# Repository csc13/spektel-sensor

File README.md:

spektel-sensor
==============
*[See the project blog here!](http://spektel.cescholz.de/)* 

This is a small project for a XMEGA based sensor for the Spektrum-RC telemetry system.

The sensor is based on the flowing components:
- Atmel XMEGA32E5
- Allegro ACS758LCB-100U hall effect current sensor
- Bosch BMP180 pressure sensor (planned)

The firmware was developed in C using Atmel Studio 6 and the Atmel ASF framework.

	Note: The Spektrum RC TM1000 telemetry modul, a DSMX receiver with data port and a 
	transmitter with telemetry functions are required to use the sensor. Not all Spektrum RC telemetry able
	transmitters support all sensors. I use a DX9 for testing.

### Basic functions
The sensor measures 25 times a second the actual current, voltage and pressure. From this 
it calculates the used capacity, hight and climb rate.

- Show used capacity of main battery
- Show actual current of main battery
- Show actual voltage of main battery
- Show altitude
- Programmable via on button (change the battery capacity)

### Planned functions
- Show climb rate
- Show cell voltages of main battery

### Project Structure
- firmware (compiled firmware for XMEGA)
- flight_logs (from Spektrum transmitter)
- hardware (Eagle PCB files)
- pictures (photos)
- project (Atmel Studio, make files, etc.)
- src (C sources)

### History
#### 2014-10-28: Initial upload with REV_A board layout
- Please note that REV_A is the initial prototype and has several bugs

#### 2014-11-02: Added support for RealtimePlotter and arduplot
Two two great serial monitors based on Processing (https://www.processing.org/).
Please see https://github.com/sebnil/RealtimePlotter.git and see https://github.com/dahart/arduplot.git).

#### 2015-01-19: Added support for the REV_B board
This includes the smaller board, BMP180 altitude measurement, setup button, self calibration.

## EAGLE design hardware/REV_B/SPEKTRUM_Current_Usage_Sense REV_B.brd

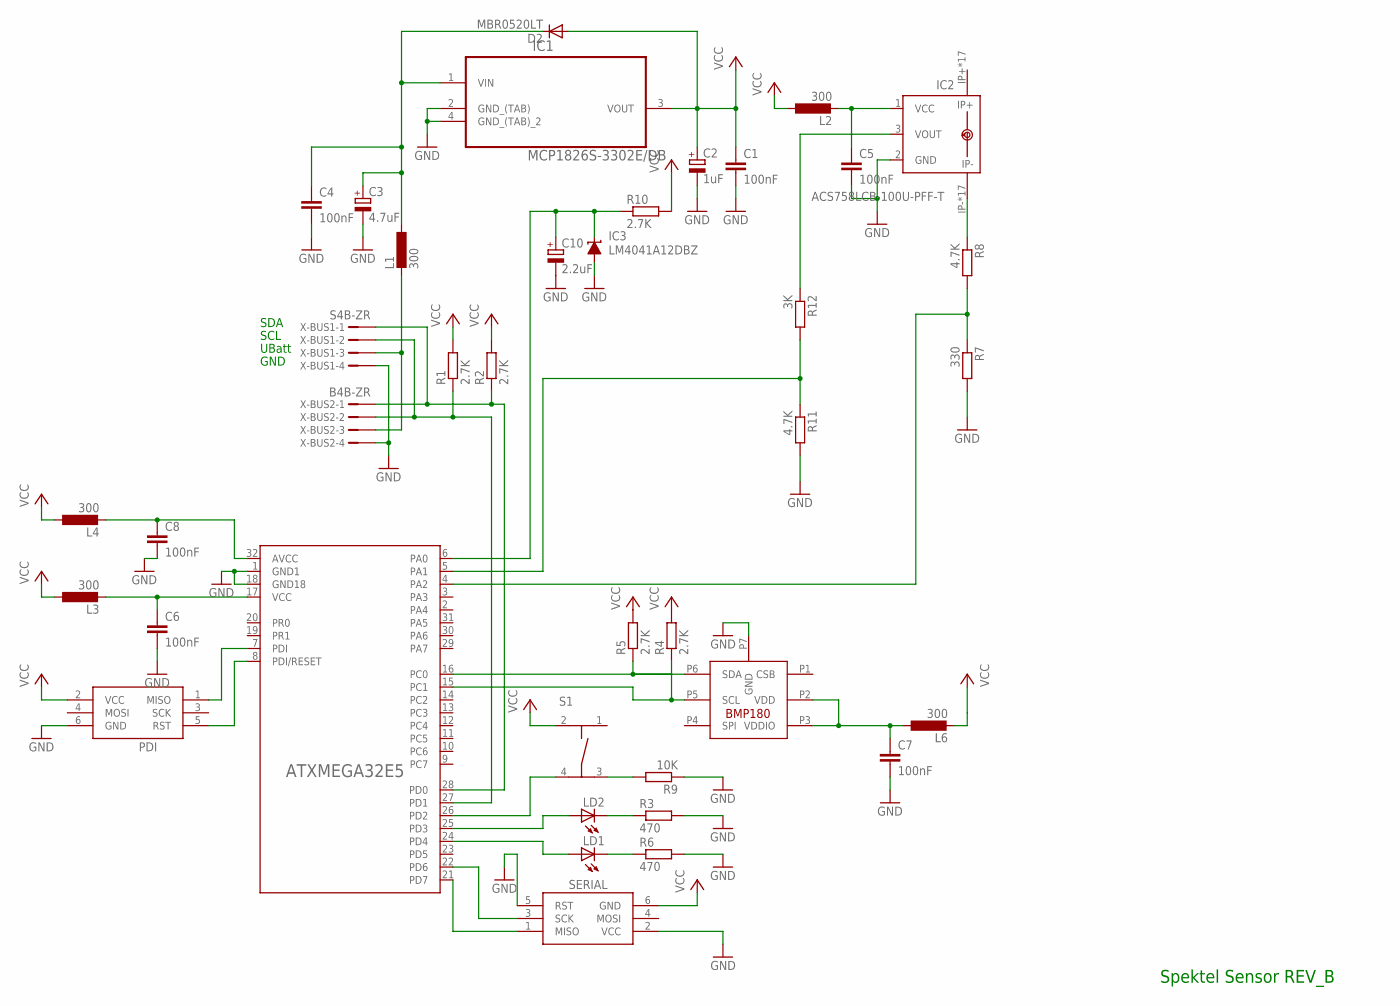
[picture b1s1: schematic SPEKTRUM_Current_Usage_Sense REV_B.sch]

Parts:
ATXMEGA32E5: ATXMEGA32E5/16E5/8E5ATXMEGA32E5-AU; TQFP32-08
BMP180: BMP180; BMP180_LGA7
C1, C4, C5, C6, C7, C8: 100nF; C0603
C2: 1uF; A/3216-18W
C3: 4.7uF; A/3216-18W
C10: 2.2uF; A/3216-18W
D2: MBR0520LT; SOD123
IC1: MCP1826S-3302E/DB; SOT230P700X180-4N
IC2: ACS758LCB-100U-PFF-T; CB-PFF; MPN ACS758LCB-100U-PFF-T
IC3: LM4041A12DBZ; DBZ_R-PDSO-G3
L1, L2, L3, L4, L6: 300; L0603
LD1, LD2: LEDCHIPLED_0603; CHIPLED_0603
PDI: AVRISP-6; AVRISP
R1, R2, R4, R5, R10: 2.7K; R0603
R3, R6: 470; R0603
R7: 330; R0603
R8, R11: 4.7K; R0603
R9: 10K; R0603
R12: 3K; R0603
S1: TASTER-9314_SMD
SERIAL: AVRISP-6; AVRISP
X-BUS1: S4B-ZR
X-BUS2: B4B-ZR

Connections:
ADC_CURRENT: ATXMEGA32E5.5 (PA1), R11.1, R12.2
ADC_VOLTAGE: ATXMEGA32E5.4 (PA2), R7.1, R8.2
AREF: ATXMEGA32E5.6 (PA0), C10.+, IC3.1 (C), R10.1
AVCCMC: ATXMEGA32E5.32 (AVCC), C8.1, L4.2
D_BUTTON: ATXMEGA32E5.26 (PD2), S1.4
GND: ATXMEGA32E5.1 (GND1), ATXMEGA32E5.18 (GND18), BMP180.P7 (GND), C1.2, C2.-, C3.-, C4.2, C5.2, C6.2, C7.2, C8.2, C10.-, IC1.2 (GND_(TAB)), IC1.4 (GND_(TAB)_2), IC2.2 (GND), IC3.2 (A), PDI.6 (GND), R3.2, R6.2, R7.2, R9.1, R11.2, SERIAL.2 (VCC), SERIAL.5 (RST), X-BUS1.4, X-BUS2.4
LED1: ATXMEGA32E5.24 (PD4), LD1.A
LED2: ATXMEGA32E5.25 (PD3), LD2.A
unnamed: L1.2, X-BUS1.3, X-BUS2.3
unnamed: LD2.C, R3.1
unnamed: C5.1, IC2.1 (VCC), L2.2
unnamed: LD1.C, R6.1
unnamed: BMP180.P2 (VDD), BMP180.P3 (VDDIO), C7.1, L6.1
unnamed: R9.2, S1.3
unnamed: IC2.3 (VOUT), R12.1
unnamed: ATXMEGA32E5.7 (PDI), PDI.1 (MISO)
unnamed: ATXMEGA32E5.8 (PDI/RESET), PDI.5 (RST)
RXD0: ATXMEGA32E5.22 (PD6), SERIAL.3 (SCK)
SENS_CUR_-: IC2.IP-, IC2.IP-@2 (IP-), IC2.IP-@3 (IP-), IC2.IP-@4 (IP-), IC2.IP-@5 (IP-), IC2.IP-@6 (IP-), IC2.IP-@7 (IP-), IC2.IP-@8 (IP-), IC2.IP-@9 (IP-), IC2.IP-@10 (IP-), IC2.IP-@11 (IP-), IC2.IP-@12 (IP-), IC2.IP-@13 (IP-), IC2.IP-@14 (IP-), IC2.IP-@15 (IP-), IC2.IP-@16 (IP-), IC2.IP-@17 (IP-), R8.1
TWIM_SCL: ATXMEGA32E5.15 (PC1), BMP180.P5 (SCL), R4.1
TWIM_SDA: ATXMEGA32E5.16 (PC0), BMP180.P6 (SDA), R5.1
TWIS_SCL: ATXMEGA32E5.27 (PD1), R1.1, X-BUS1.2, X-BUS2.2
TWIS_SDA: ATXMEGA32E5.28 (PD0), R2.1, X-BUS1.1, X-BUS2.1
TXD0: ATXMEGA32E5.21 (PD7), SERIAL.1 (MISO)
UBATT: C3.+, C4.1, D2.C, IC1.1 (VIN), L1.1
VCC: C1.1, C2.+, D2.A, IC1.3 (VOUT), L2.1, L3.1, L4.1, L6.2, PDI.2 (VCC), R1.2, R2.2, R4.2, R5.2, R10.2, S1.2, SERIAL.6 (GND)
VCCMC: ATXMEGA32E5.17 (VCC), C6.1, L3.2

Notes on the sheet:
SDA
SCL
UBatt
GND
Spektel Sensor REV_B

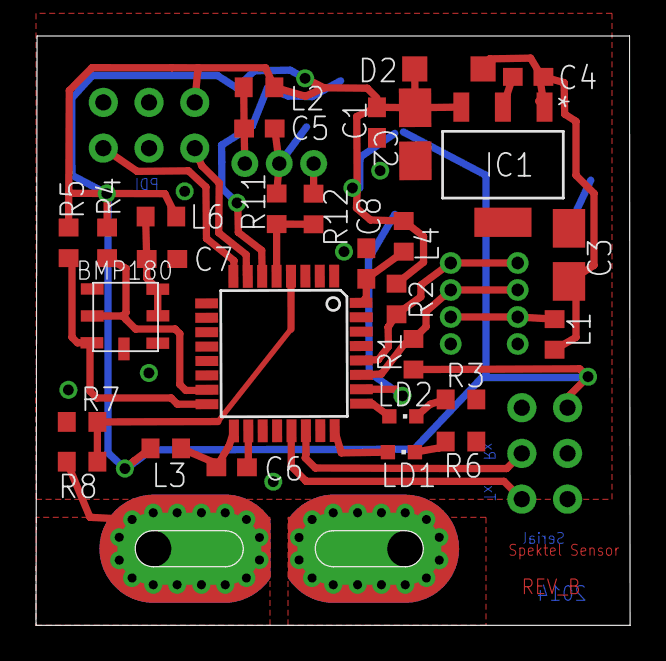
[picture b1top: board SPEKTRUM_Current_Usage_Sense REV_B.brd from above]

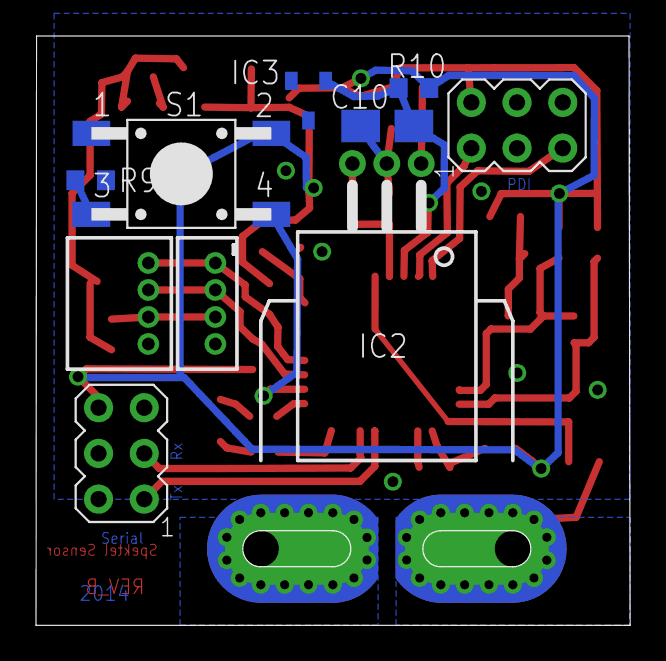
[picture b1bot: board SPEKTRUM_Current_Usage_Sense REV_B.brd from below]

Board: 2 copper layers, 33.0 x 32.7 mm, 39 parts (10 on the bottom side), 27 nets.

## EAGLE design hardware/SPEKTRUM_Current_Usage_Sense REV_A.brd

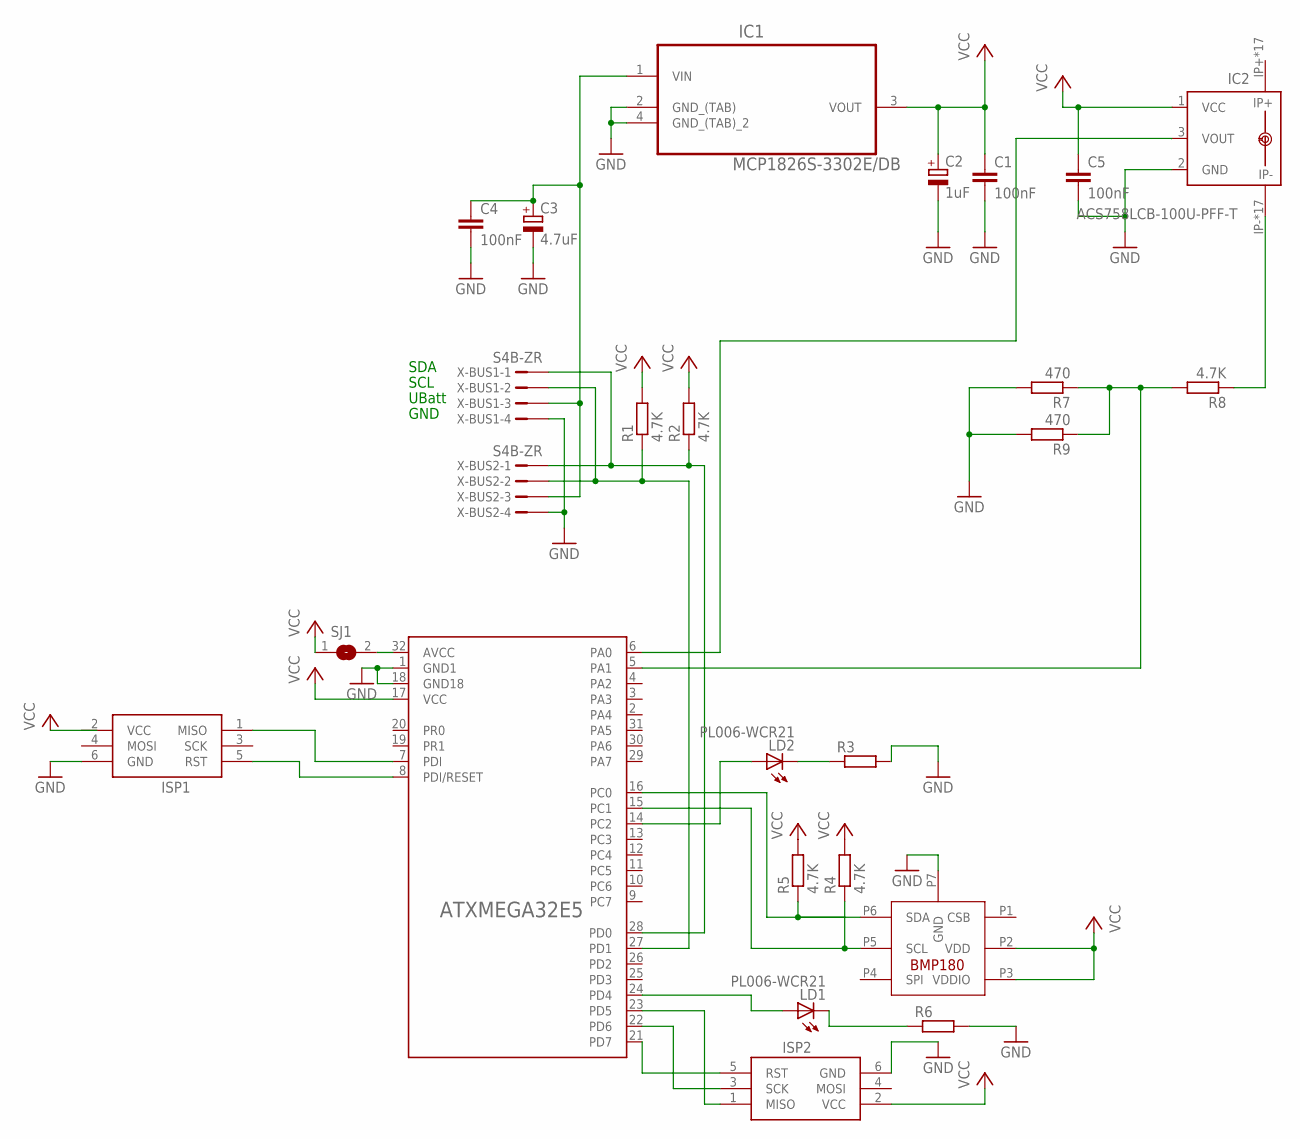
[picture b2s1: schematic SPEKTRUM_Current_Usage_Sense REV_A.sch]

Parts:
ATXMEGA32E5: ATXMEGA32E5/16E5/8E5ATXMEGA32E5-AU; TQFP32-08
C1, C4, C5: 100nF; C0603
C2: 1uF; A/3216-18W
C3: 4.7uF; A/3216-18W
IC1: MCP1826S-3302E/DB; SOT230P700X180-4N
IC2: ACS758LCB-100U-PFF-T; CB-PFF; MPN ACS758LCB-100U-PFF-T
ISP1, ISP2: AVRISP-6; AVRISP
LD1, LD2: PL006-WCR21; SOT23
R1, R2, R4, R5, R8: 4.7K; M1206
R3, R6: R-EU_M1206; M1206
R7, R9: 470; M1206
SJ1: SJ
U$1: BMP180; BMP180_LGA7
X-BUS1, X-BUS2: S4B-ZR

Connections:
GND: ATXMEGA32E5.1 (GND1), ATXMEGA32E5.18 (GND18), C1.2, C2.-, C3.-, C4.2, C5.2, IC1.2 (GND_(TAB)), IC1.4 (GND_(TAB)_2), IC2.2 (GND), ISP1.6 (GND), ISP2.6 (GND), R3.2, R6.2, R7.2, R9.2, U$1.P7 (GND), X-BUS1.4, X-BUS2.4
unnamed: ATXMEGA32E5.6 (PA0), IC2.3 (VOUT)
unnamed: C3.+, C4.1, IC1.1 (VIN), X-BUS1.3, X-BUS2.3
unnamed: LD2.1 (C), R3.1
unnamed: ATXMEGA32E5.27 (PD1), R1.1, X-BUS1.2, X-BUS2.2
unnamed: ATXMEGA32E5.28 (PD0), R2.1, X-BUS1.1, X-BUS2.1
unnamed: LD1.1 (C), R6.1
unnamed: ATXMEGA32E5.14 (PC2), LD2.3 (A)
unnamed: ATXMEGA32E5.16 (PC0), R5.1, U$1.P6 (SDA)
unnamed: ATXMEGA32E5.15 (PC1), R4.1, U$1.P5 (SCL)
unnamed: ATXMEGA32E5.7 (PDI), ISP1.1 (MISO)
unnamed: ATXMEGA32E5.8 (PDI/RESET), ISP1.5 (RST)
unnamed: ATXMEGA32E5.24 (PD4), LD1.3 (A)
unnamed: ATXMEGA32E5.32 (AVCC), SJ1.2
unnamed: IC2.IP-, IC2.IP-@2 (IP-), IC2.IP-@3 (IP-), IC2.IP-@4 (IP-), IC2.IP-@5 (IP-), IC2.IP-@6 (IP-), IC2.IP-@7 (IP-), IC2.IP-@8 (IP-), IC2.IP-@9 (IP-), IC2.IP-@10 (IP-), IC2.IP-@11 (IP-), IC2.IP-@12 (IP-), IC2.IP-@13 (IP-), IC2.IP-@14 (IP-), IC2.IP-@15 (IP-), IC2.IP-@16 (IP-), IC2.IP-@17 (IP-), R8.1
unnamed: ATXMEGA32E5.5 (PA1), R7.1, R8.2, R9.1
unnamed: ATXMEGA32E5.21 (PD7), ISP2.5 (RST)
unnamed: ATXMEGA32E5.22 (PD6), ISP2.3 (SCK)
unnamed: ATXMEGA32E5.23 (PD5), ISP2.1 (MISO)
VCC: ATXMEGA32E5.17 (VCC), C1.1, C2.+, C5.1, IC1.3 (VOUT), IC2.1 (VCC), ISP1.2 (VCC), ISP2.2 (VCC), R1.2, R2.2, R4.2, R5.2, SJ1.1, U$1.P2 (VDD), U$1.P3 (VDDIO)

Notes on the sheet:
SDA
SCL
UBatt
GND

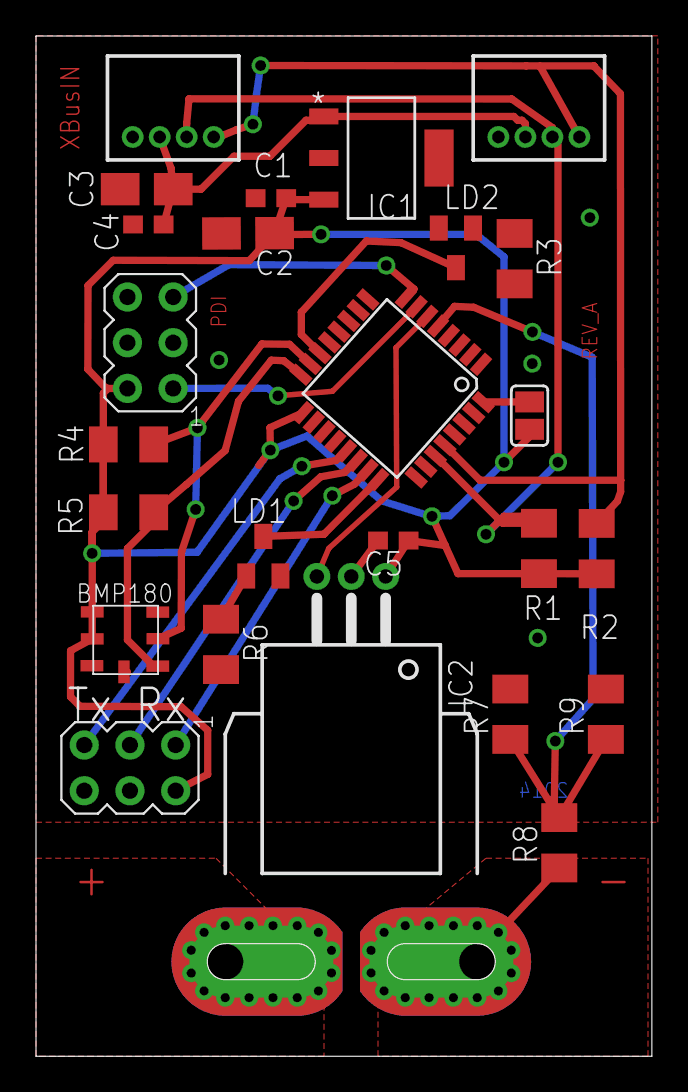
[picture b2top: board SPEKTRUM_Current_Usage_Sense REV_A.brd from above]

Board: 2 copper layers, 34.2 x 56.7 mm, 25 parts (0 on the bottom side), 20 nets.

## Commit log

2014-10-18 Update README.md
    Initial
2014-10-28 Initial upload of project
    Initial upload with BOARD REV_A
2014-10-28 Update README.md
    Added file system structure description
2014-10-28 Added picture of sensor
2014-10-28 Added picture folder
2014-10-28 Added png images for PCB layout and schematics
2014-10-31 Added lowpass filter for testing
2014-11-02 Added filtering
    Added lowpass to voltage measurement
    Corrected measurements by adding 10% to current measurement after test
    flight.
2014-11-02 Added support for serial plotters
    RealtimePlotter and Arduplot, both based on Processing
    Added updated flight log
2014-11-02 Correction of Readme
2014-11-20 New board revision B
2014-11-20 Change
2014-11-20 Corrected
2014-11-20 Create gh-pages branch via GitHub
2014-11-23 image
2014-11-23 New jekyll theme and new posts
2014-11-23 Change to jekyll
2014-11-23 gitignore
2014-11-23 change jekyll config
2014-11-24 Changed to Balzac Theme for GitHub Pages
2014-11-24 Changed images
2014-11-24 gemfile
2014-11-24 changed _config
2014-11-24 CNAME
2014-11-25 Added flight log picture
2014-11-25 Added link to blog
2014-11-25 Changed last post
2014-11-25 Changed About page
2014-11-26 Changed About page
    Added background
2014-11-26 Added pot on XMEGA
2014-11-27 Changed feature image
2014-11-27 Correction
2014-12-14 Added Assembly Plan for REV_B board
2014-12-23 Changed assembly plan
2014-12-23 New post hardware assembly
2014-12-24 New Post Firmware Part 1
2014-12-31 Added post Sensor setup
2014-12-31 Added hook up diagram
2014-12-31 added restrictions section
2015-01-04 Added post on TWI communication
2015-01-19 Added tips for BMP180 assembly and setup
2015-01-19 Added new sources and project file
    Support for REV_B board
    Sensor with BMP180 altitude display, setup via button, self calibration
2015-01-19 REV_B support
2015-02-22 Added support for the Flight pack capacity sensor
    and some i2c protocols
2015-02-22 New post: getting the parts
2015-02-22 Correct
2015-02-23 Added Software Part 2 post
2015-02-23 Extend flight log
    New flights with the altitude
2015-02-23 Added new post explaining the capacity measurement
    Added new post and some corrections for the new Flight pack
    capacity sensor.
